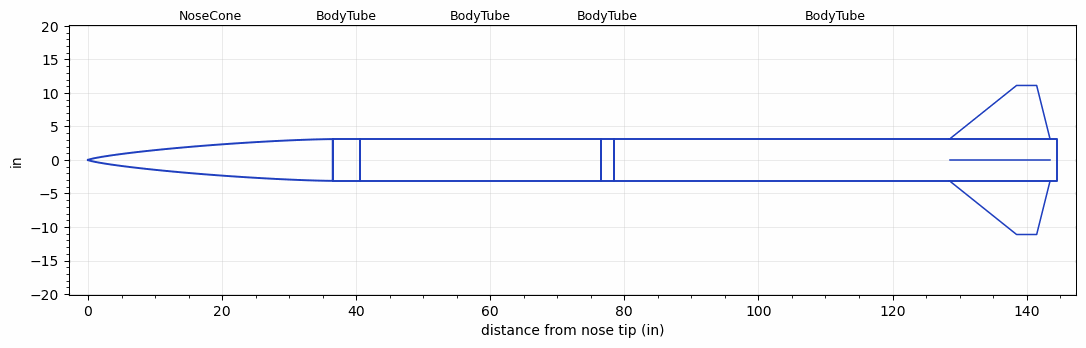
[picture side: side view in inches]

<RASAeroDocument>
 <FileVersion>2</FileVersion>
 <RocketDesign>
  <NoseCone>
   <Length>36.5</Length>
   <Diameter>6.23</Diameter>
   <Shape>Von Karman Ogive</Shape>
   <BluntRadius>0.075</BluntRadius>
   <Location>0</Location>
  </NoseCone>
  <BodyTube>
   <Length>4</Length>
   <Diameter>6.23</Diameter>
   <Location>36.5</Location>
  </BodyTube>
  <BodyTube>
   <Length>36</Length>
   <Diameter>6.23</Diameter>
   <Location>40.5</Location>
  </BodyTube>
  <BodyTube>
   <Length>2</Length>
   <Diameter>6.23</Diameter>
   <Location>76.5</Location>
  </BodyTube>
  <BodyTube>
   <Length>66</Length>
   <Diameter>6.23</Diameter>
   <RailGuideDiameter>0.5</RailGuideDiameter>
   <RailGuideHeight>0.56</RailGuideHeight>
   <Location>78.5</Location>
   <Fin>
    <Count>4</Count>
    <Chord>15</Chord>
    <Span>8</Span>
    <SweepDistance>10</SweepDistance>
    <TipChord>3</TipChord>
    <Thickness>0.375</Thickness>
    <LERadius>0.025</LERadius>
    <Location>16</Location>
    <AirfoilSection>Double Wedge</AirfoilSection>
    <FX1>1</FX1>
    <FX3>1</FX3>
   </Fin>
   <Protuberance>
    <StreamlinedNoBaseDrag>0</StreamlinedNoBaseDrag>
    <StreamlinedWithBaseDrag>0</StreamlinedWithBaseDrag>
    <InclinedPlate1Angle>45</InclinedPlate1Angle>
    <InclinedPlate1FrontalArea>2</InclinedPlate1FrontalArea>
    <InclinedPlate2Angle>0</InclinedPlate2Angle>
    <InclinedPlate2FrontalArea>0</InclinedPlate2FrontalArea>
   </Protuberance>
  </BodyTube>
  <Surface>Camouflage Paint</Surface>
  <ModifiedBarrowman>False</ModifiedBarrowman>
  <Turbulence>False</Turbulence>
  <UseBooster1>False</UseBooster1>
  <UseBooster2>False</UseBooster2>
  <Comments>Includes new fin geometry to remove tip rake angle to allow for more accurate RasAero simluation verification</Comments>
 </RocketDesign>
 <LaunchSite>
  <Altitude>2930</Altitude>
  <Pressure>0</Pressure>
  <RodAngle>4</RodAngle>
  <RodLength>17</RodLength>
  <Temperature>95</Temperature>
  <WindSpeed>8</WindSpeed>
 </LaunchSite>
 <Recovery>
  <Altitude1>1500</Altitude1>
  <Altitude2>1500</Altitude2>
  <DeviceType1>Parachute</DeviceType1>
  <DeviceType2>Parachute</DeviceType2>
  <Event1>True</Event1>
  <Event2>True</Event2>
  <Size1>119.9998</Size1>
  <Size2>24</Size2>
  <EventType1>Altitude</EventType1>
  <EventType2>Altitude</EventType2>
  <CD1>1.16</CD1>
  <CD2>0</CD2>
 </Recovery>
 <SimulationList>
  <Simulation>
   <SustainerEngine>O4176  (EX)</SustainerEngine>
   <SustainerLaunchWt>136</SustainerLaunchWt>
   <SustainerNozzleDiameter>2.8</SustainerNozzleDiameter>
   <SustainerCG>101</SustainerCG>
   <SustainerIgnitionDelay>0</SustainerIgnitionDelay>
   <Booster1SeparationDelay>0</Booster1SeparationDelay>
   <Booster1IgnitionDelay>0</Booster1IgnitionDelay>
   <IncludeBooster1>False</IncludeBooster1>
   <Booster2Delay>0</Booster2Delay>
   <IncludeBooster2>False</IncludeBooster2>
   <TimetoApogee>44.85848</TimetoApogee>
   <MaxAltitude>33013.2</MaxAltitude>
   <MaxVelocity>1835.926</MaxVelocity>
   <OptimumWt>75.42841</OptimumWt>
   <OptimumMaxAlt>75.42841</OptimumMaxAlt>
  </Simulation>
  <Simulation>
   <SustainerLaunchWt>138.5684</SustainerLaunchWt>
   <SustainerCG>94.979</SustainerCG>
   <SustainerIgnitionDelay>0</SustainerIgnitionDelay>
   <Booster1SeparationDelay>0</Booster1SeparationDelay>
   <Booster1IgnitionDelay>0</Booster1IgnitionDelay>
   <IncludeBooster1>False</IncludeBooster1>
   <Booster2Delay>0</Booster2Delay>
   <IncludeBooster2>False</IncludeBooster2>
  </Simulation>
  <Simulation>
   <SustainerLaunchWt>138.5684</SustainerLaunchWt>
   <SustainerCG>94.979</SustainerCG>
   <SustainerIgnitionDelay>0</SustainerIgnitionDelay>
   <Booster1SeparationDelay>0</Booster1SeparationDelay>
   <Booster1IgnitionDelay>0</Booster1IgnitionDelay>
   <IncludeBooster1>False</IncludeBooster1>
   <Booster2Delay>0</Booster2Delay>
   <IncludeBooster2>False</IncludeBooster2>
  </Simulation>
 </SimulationList>
</RASAeroDocument>
